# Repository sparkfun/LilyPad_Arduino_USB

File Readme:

LilyPad Arduino USB

This repository contains all of the design files for the LilyPad Arduino USB.

The "Firmware" directory contains a reference copy of the bootloader; the
"official" maintained version is in the Arduino source project. We'll try to
keep this updated if anything changes.

As with all SparkFun developments, we consider this to be "beerware"- should
you reuse it, please buy us a pint (of beer, orange juice, or braehg) at the
local next time you see one of us.

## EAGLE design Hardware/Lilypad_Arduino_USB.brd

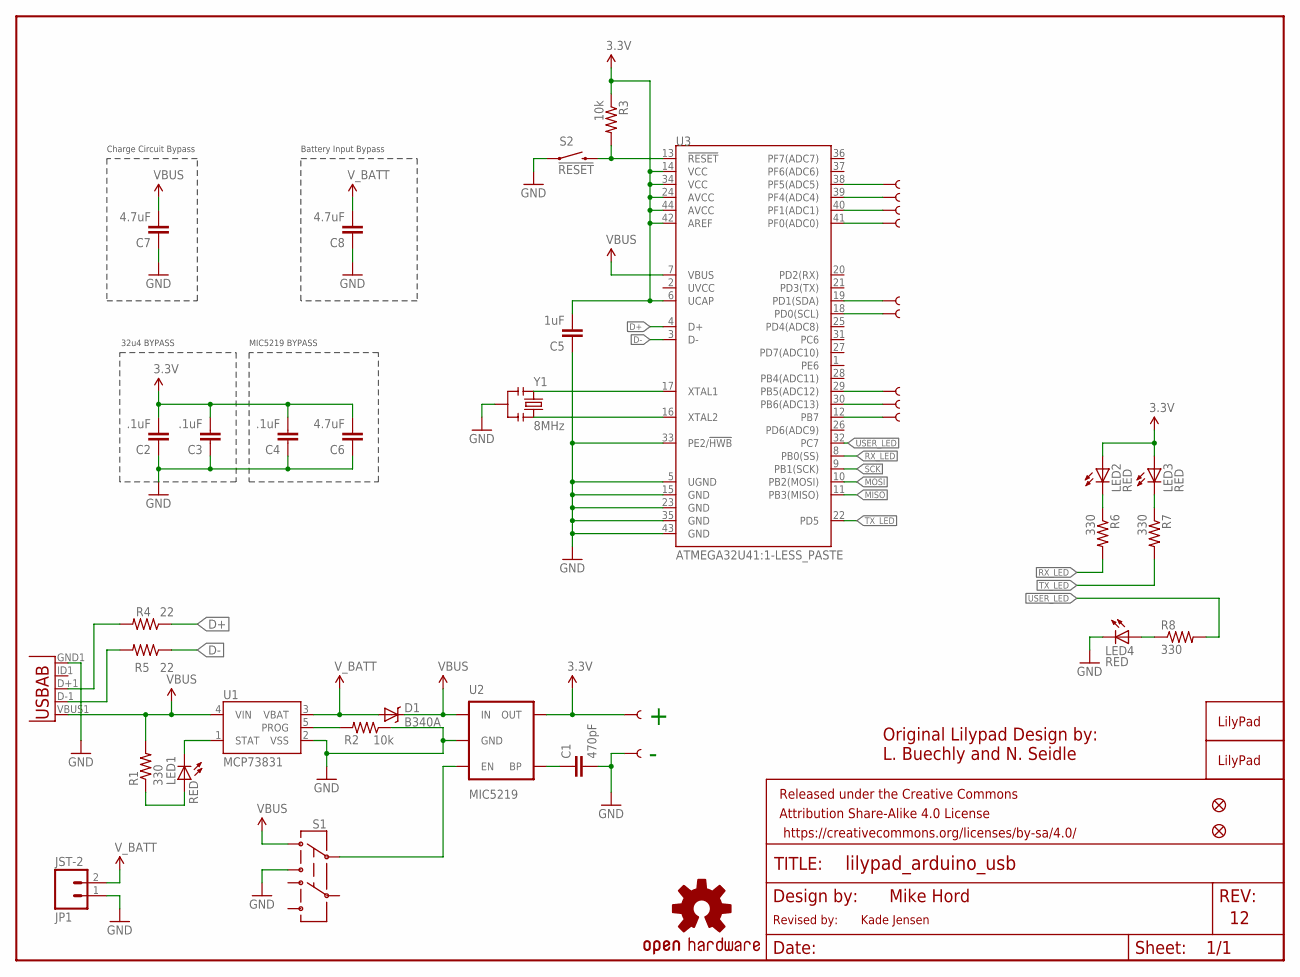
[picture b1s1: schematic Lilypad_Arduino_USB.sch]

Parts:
+: SEWTAP9; PETAL-LONG-1-2SIDE
-: SEWTAP9; PETAL-LONG-1-2SIDE
A2, A3, A4, A5: SEWTAP9; PETAL-LONG-1-2SIDE
C1: 470pF; 0603-CAP
C2, C3, C4: .1uF; 0603-CAP
C5: 1uF; 0603-CAP
C6: 4.7uF; 0603-CAP
C7, C8: 4.7uF; 1206
D1: B340A; SMA-DIODE
D5, D6, D9, D10, D11: SEWTAP9; PETAL-LONG-1-2SIDE
FRAME1: FRAME-LETTER; CREATIVE_COMMONS
JP1: JST-2; JST-2-SMD
JP2, JP3: FIDUCIAL1X2; FIDUCIAL-1X2
LED1, LED2, LED3, LED4: RED; LED-0603
R1, R6, R7, R8: 330; 0603-RES
R2, R3: 10k; 0603-RES
R4, R5: 22; 0603-RES
S1: SWITCH-DPDTAYZ0202; AYZ0202
S2: !RESET; TACTILE_SWITCH_SMD
U1: MCP73831; SOT23-5
U2: MIC5219; SOT23-5
U3: ATMEGA32U41:1-LESS_PASTE; QFN-44-NOPAD_1:1-LESS_PASTE
U5: USB-ABCONN-11794; USB-AB-MICRO-SMD_V03
U$1: LOGO-LPLPA; LOGO-LPA
U$5: OSHW-LOGOM; OSHW-LOGO-M
U$13: LOGO-LPLP; LOGO-LILYPAD
Y1: 8MHz; RESONATOR-SMD

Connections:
3.3V: +.1, C2.2, C3.2, C4.2, C5.2, C6.2, LED2.A, LED3.A, R3.1, U2.5 (OUT), U3.6 (UCAP), U3.14 (VCC), U3.24 (AVCC), U3.34 (VCC), U3.42 (AREF), U3.44 (AVCC)
5V: C7.2, D1.C, R1.2, S1.1, U1.4 (VIN), U2.1 (IN), U3.7 (VBUS), U5.VBUS1 (VBUS)
D+: R4.1, U3.4 (D+)
D-: R5.1, U3.3 (D-)
GND: -.1, C1.2, C2.1, C3.1, C4.1, C5.1, C6.1, C7.1, C8.1, JP1.1 (2), LED4.C, R2.1, S1.3, S2.1, U1.2 (VSS), U2.2 (GND), U3.5 (UGND), U3.15 (GND), U3.23 (GND), U3.33 (PE2/!HWB), U3.35 (GND), U3.43 (GND), U5.GND1 (GND), Y1.2
MISO: U3.11 (PB3(MISO))
MOSI: U3.10 (PB2(MOSI))
unnamed: LED2.C, R6.1
unnamed: S1.2, U2.3 (EN)
unnamed: LED1.A, R1.1
unnamed: LED1.C, U1.1 (STAT)
unnamed: U3.17 (XTAL1), Y1.1
unnamed: R2.2, U1.5 (PROG)
unnamed: U3.16 (XTAL2), Y1.3
unnamed: C1.1, U2.4 (BP)
unnamed: D11.1, U3.12 (PB7)
unnamed: D10.1, U3.30 (PB6(ADC13))
unnamed: D9.1, U3.29 (PB5(ADC12))
unnamed: D5.1, U3.19 (PD1(SDA))
unnamed: D6.1, U3.18 (PD0(SCL))
unnamed: A5.1, U3.41 (PF0(ADC0))
unnamed: A4.1, U3.40 (PF1(ADC1))
unnamed: A3.1, U3.39 (PF4(ADC4))
unnamed: A2.1, U3.38 (PF5(ADC5))
unnamed: LED4.A, R8.1
unnamed: R5.2, U5.D-1 (D-)
unnamed: R4.2, U5.D+1 (D+)
unnamed: LED3.C, R7.1
RESET: R3.2, S2.3 (2), U3.13 (!RESET)
RX_LED: R6.2, U3.8 (PB0(SS))
SCK: U3.9 (PB1(SCK))
TX_LED: R7.2, U3.22 (PD5)
USER_LED: R8.2, U3.32 (PC7)
V_BATT: C8.2, D1.A, JP1.2 (1), U1.3 (VBAT)

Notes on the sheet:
32u4 BYPASS
MIC5219 BYPASS
Mike Hord
Original Lilypad Design by:
L. Buechly and N. Seidle
Charge Circuit Bypass
Battery Input Bypass
Revised by:
Kade Jensen

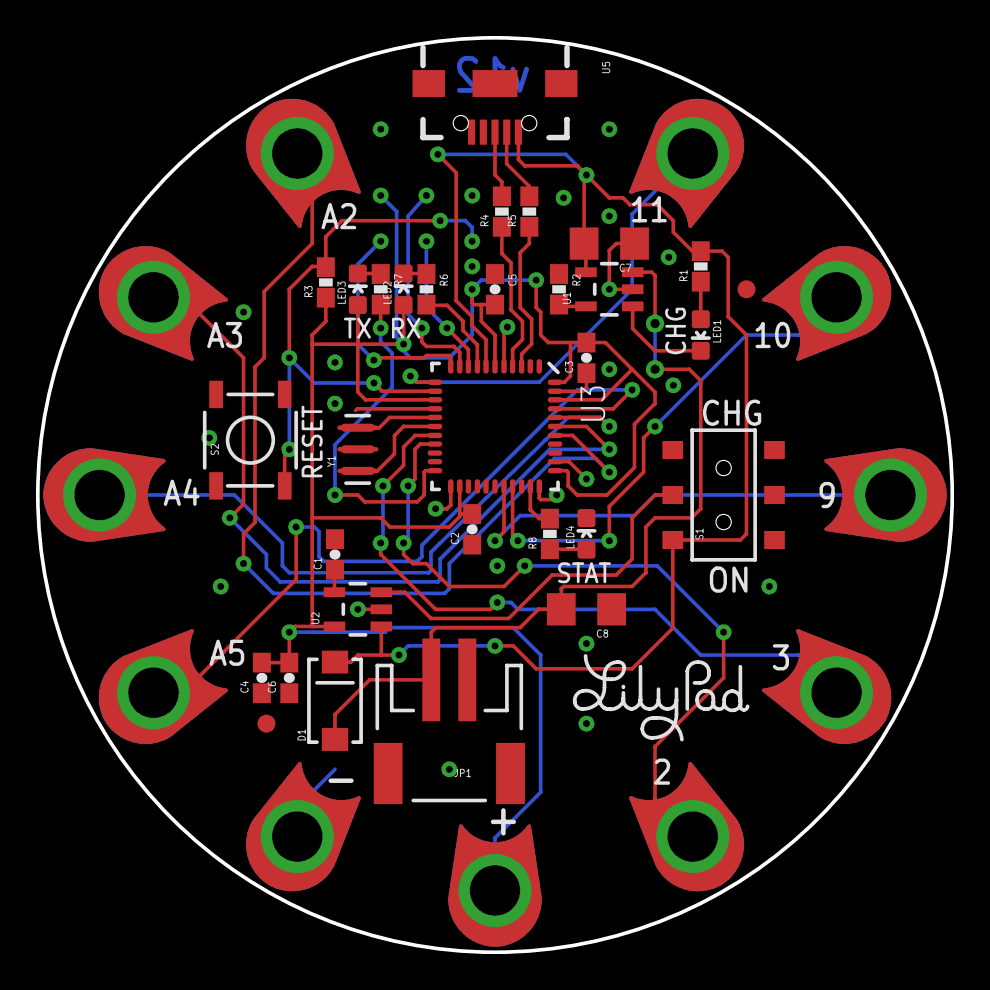
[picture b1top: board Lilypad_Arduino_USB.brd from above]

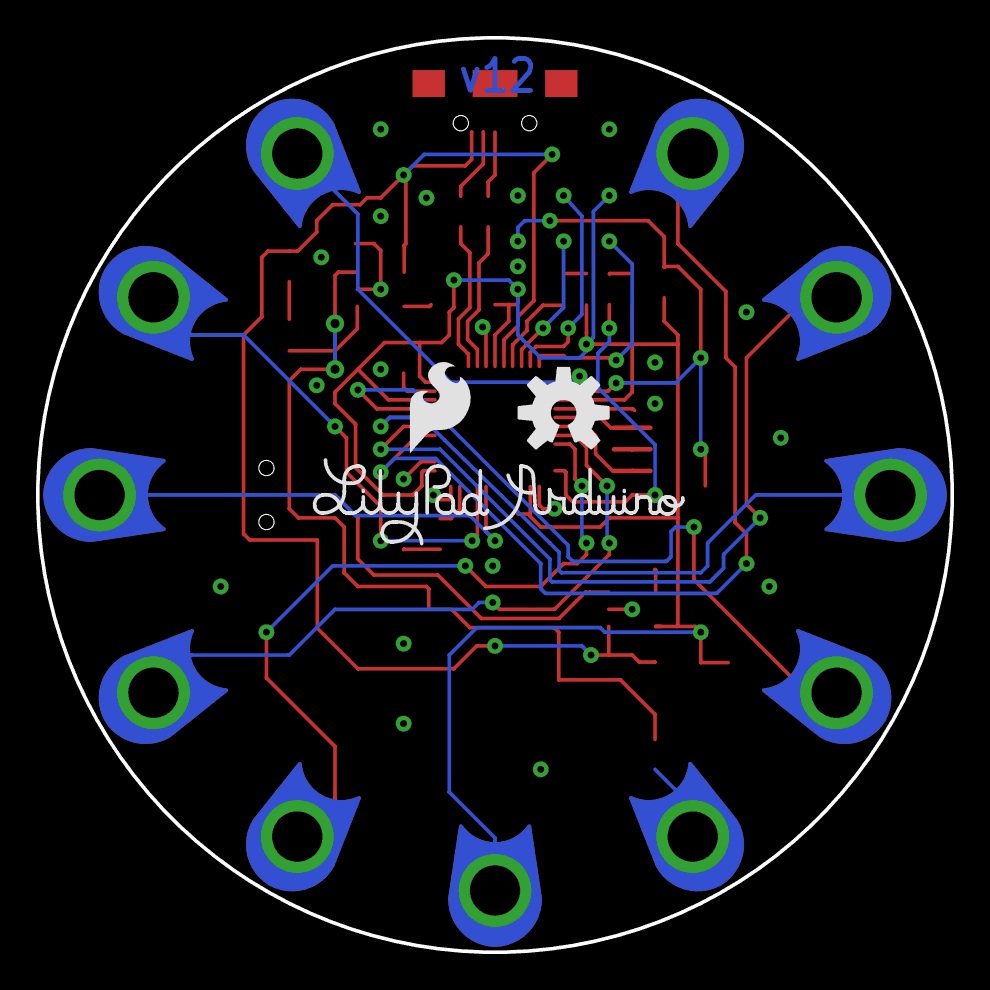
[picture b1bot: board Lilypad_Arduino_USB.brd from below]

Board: 2 copper layers, 50.8 x 50.8 mm, 47 parts (3 on the bottom side), 31 nets.

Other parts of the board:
U$7: SFE_LOGO_FLAME_.2

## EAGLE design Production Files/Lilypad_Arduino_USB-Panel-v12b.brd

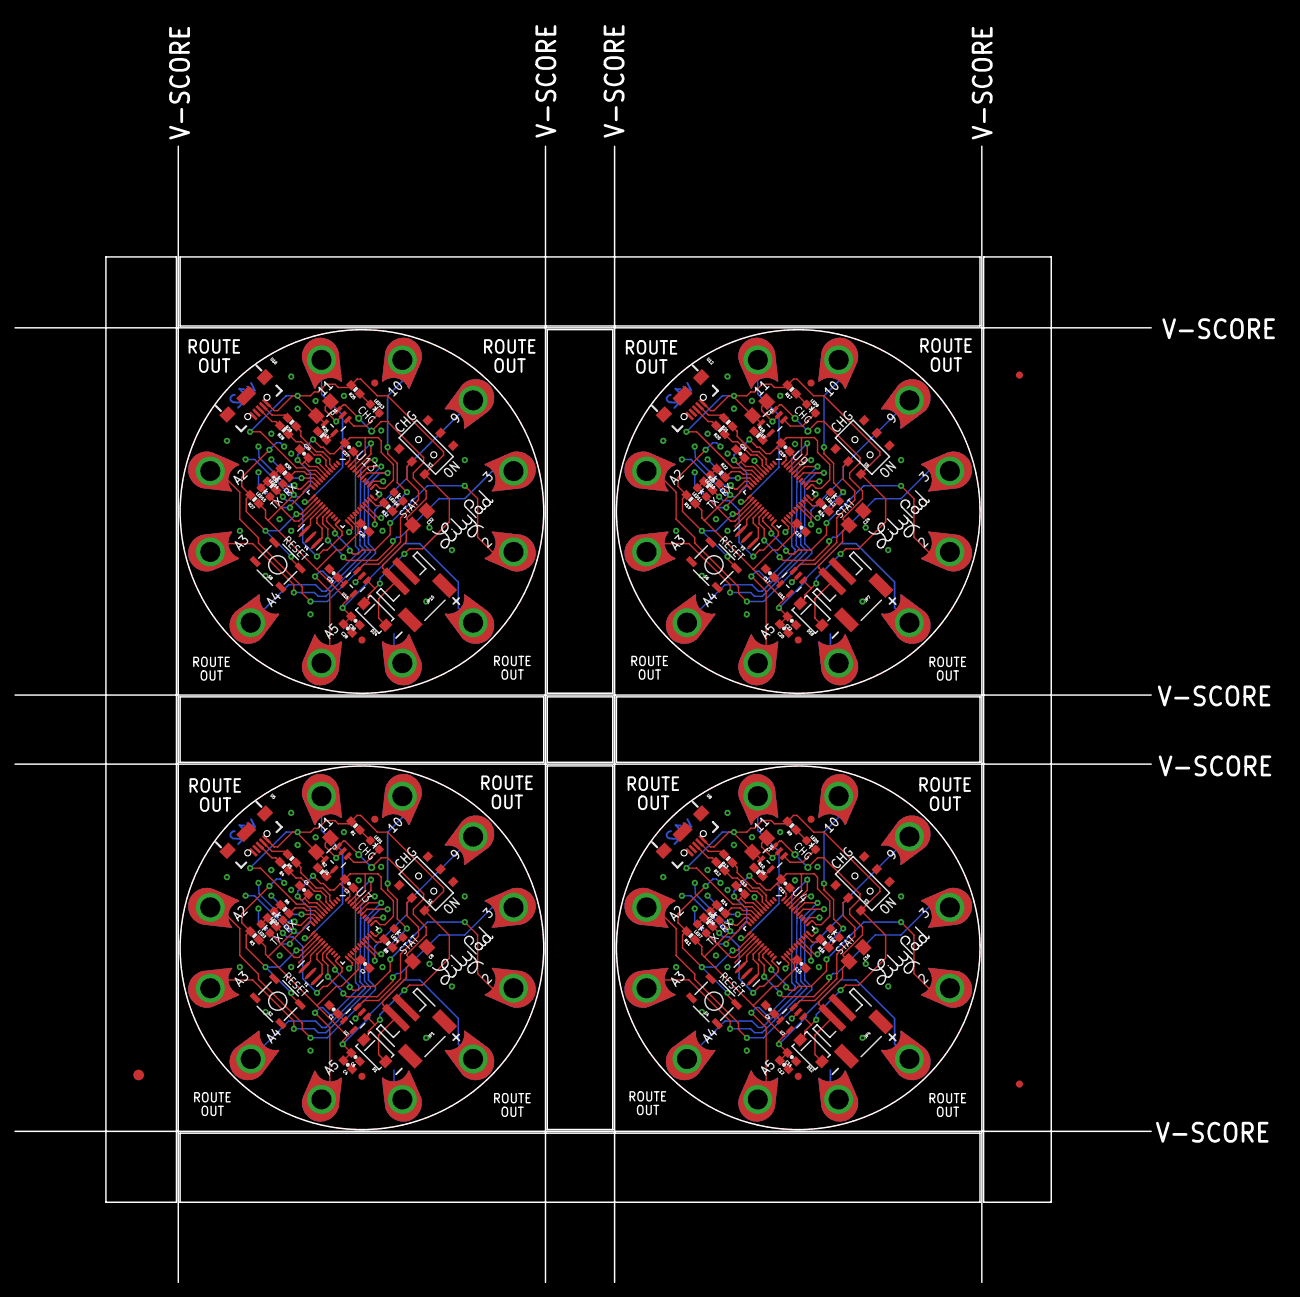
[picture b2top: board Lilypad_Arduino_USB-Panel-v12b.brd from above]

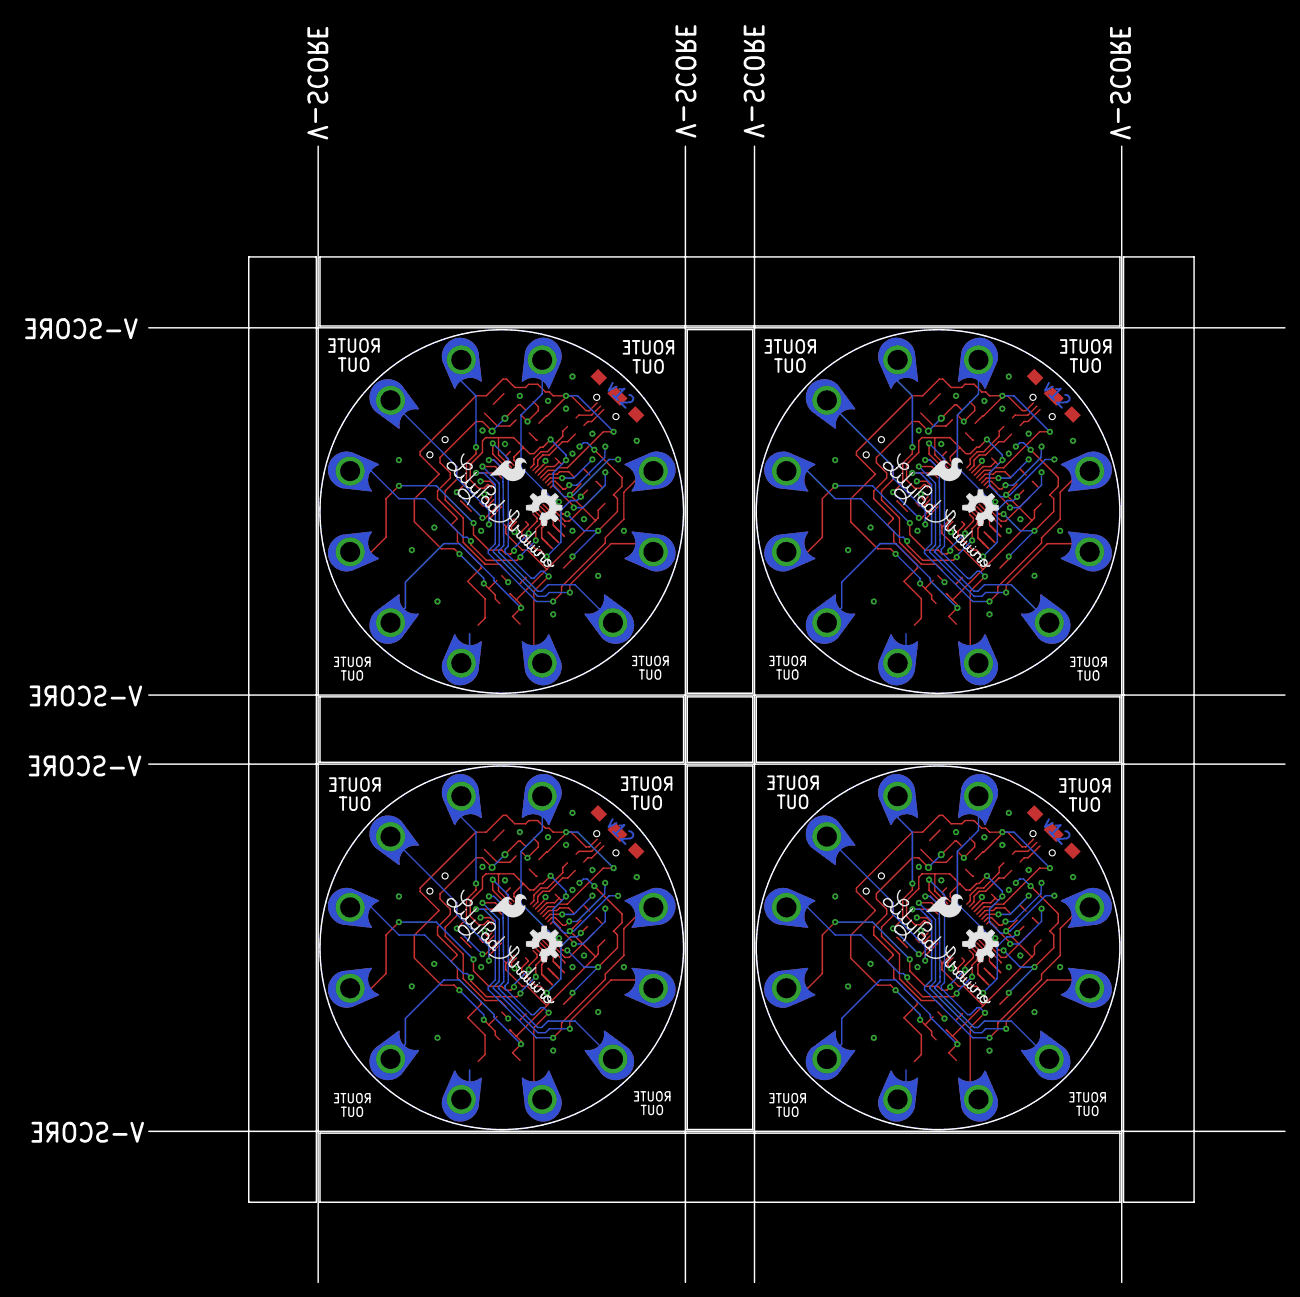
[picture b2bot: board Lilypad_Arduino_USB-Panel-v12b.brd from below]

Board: 2 copper layers, 158.8 x 158.8 mm, 187 parts (12 on the bottom side), 124 nets.

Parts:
+, +1, +2, +3: SEWTAP9; PETAL-LONG-1-2SIDE
-, -1, -2, -3: SEWTAP9; PETAL-LONG-1-2SIDE
A1, A2, A3, A4, A5, A6, A7, A8, A9, A10, A11, A12, A13, A14, A15, A16: SEWTAP9; PETAL-LONG-1-2SIDE
C1, C9, C17, C25: 470pF; 0603-CAP
C2, C3, C4, C10, C11, C12, C18, C19, C20, C26, C27, C28: .1uF; 0603-CAP
C5, C13, C21, C29: 1uF; 0603-CAP
C6, C14, C22, C30: 4.7uF; 0603-CAP
C7, C8, C15, C16, C23, C24, C31, C32: 4.7uF; 1206
D1, D12, D18, D24: B340A; SMA-DIODE
D2, D3, D4, D5, D6, D7, D8, D9, D10, D11, D13, D14, D15, D16, D17, D19, D20, D21, D22, D23: SEWTAP9; PETAL-LONG-1-2SIDE
E$1: FIDUCIAL-1.5X3
E$3, E$5: FIDUCIAL-1X2
JP1, JP4, JP7, JP10: JST-2; JST-2-SMD
JP2, JP3, JP5, JP6, JP8, JP9, JP11, JP12: FIDUCIAL1X2; FIDUCIAL-1X2
LED1, LED2, LED3, LED4, LED5, LED6, LED7, LED8, LED9, LED10, LED11, LED12, LED13, LED14, LED15, LED16: RED; LED-0603
R1, R6, R7, R8, R9, R14, R15, R16, R17, R22, R23, R24, R25, R30, R31, R32: 330; 0603-RES
R2, R3, R10, R11, R18, R19, R26, R27: 10k; 0603-RES
R4, R5, R12, R13, R20, R21, R28, R29: 22; 0603-RES
S1, S3, S5, S7: AYZ0202
S2, S4, S6, S8: !RESET; TACTILE_SWITCH_SMD
U1, U6, U10, U14: MCP73831; SOT23-5
U2, U7, U11, U15: MIC5219; SOT23-5
U3, U4, U9, U13: ATMEGA32U41:1-LESS_PASTE; QFN-44-NOPAD_1:1-LESS_PASTE
U5, U8, U12, U16: USB-AB-MICRO-SMD_V03
U$1, U$3, U$9, U$14: LOGO-LPLPA; LOGO-LPA
U$2, U$8, U$12, U$13: LOGO-LPLP; LOGO-LILYPAD
U$4, U$5, U$10, U$15: OSHW-LOGOM; OSHW-LOGO-M
U$6, U$7, U$11, U$16: SFE_LOGO_FLAME_.2
Y1, Y2, Y3, Y4: 8MHz; RESONATOR-SMD

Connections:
3.3V: +.1, C2.2, C3.2, C4.2, C5.2, C6.2, LED2.A, LED3.A, R3.1, U2.5, U3.6, U3.14, U3.24, U3.34, U3.42, U3.44
3.3V1: +1.1, C10.2, C11.2, C12.2, C13.2, C14.2, LED6.A, LED7.A, R11.1, U4.6, U4.14, U4.24, U4.34, U4.42, U4.44, U7.5
3.3V2: +2.1, C18.2, C19.2, C20.2, C21.2, C22.2, LED10.A, LED11.A, R19.1, U9.6, U9.14, U9.24, U9.34, U9.42, U9.44, U11.5
3.3V3: +3.1, C26.2, C27.2, C28.2, C29.2, C30.2, LED14.A, LED15.A, R27.1, U13.6, U13.14, U13.24, U13.34, U13.42, U13.44, U15.5
5V: C7.2, D1.C, R1.2, S1.1, U1.4, U2.1, U3.7, U5.VBUS1
5V1: C15.2, D12.C, R9.2, S3.1, U4.7, U6.4, U7.1, U8.VBUS1
5V2: C23.2, D18.C, R17.2, S5.1, U9.7, U10.4, U11.1, U12.VBUS1
5V3: C31.2, D24.C, R25.2, S7.1, U13.7, U14.4, U15.1, U16.VBUS1
D+: R4.1, U3.4
D+1: R12.1, U4.4
D+2: R20.1, U9.4
D+3: R28.1, U13.4
D-: R5.1, U3.3
D-1: R13.1, U4.3
D-2: R21.1, U9.3
D-3: R29.1, U13.3
GND: -.1, C1.2, C2.1, C3.1, C4.1, C5.1, C6.1, C7.1, C8.1, JP1.1, LED4.C, R2.1, S1.3, S2.1, U1.2, U2.2, U3.5, U3.15, U3.23, U3.33, U3.35, U3.43, U5.GND1, Y1.2
GND1: -1.1, C9.2, C10.1, C11.1, C12.1, C13.1, C14.1, C15.1, C16.1, JP4.1, LED8.C, R10.1, S3.3, S4.1, U4.5, U4.15, U4.23, U4.33, U4.35, U4.43, U6.2, U7.2, U8.GND1, Y2.2
GND2: -2.1, C17.2, C18.1, C19.1, C20.1, C21.1, C22.1, C23.1, C24.1, JP7.1, LED12.C, R18.1, S5.3, S6.1, U9.5, U9.15, U9.23, U9.33, U9.35, U9.43, U10.2, U11.2, U12.GND1, Y3.2
GND3: -3.1, C25.2, C26.1, C27.1, C28.1, C29.1, C30.1, C31.1, C32.1, JP10.1, LED16.C, R26.1, S7.3, S8.1, U13.5, U13.15, U13.23, U13.33, U13.35, U13.43, U14.2, U15.2, U16.GND1, Y4.2
unnamed: LED2.C, R6.1
unnamed: S1.2, U2.3
unnamed: LED1.A, R1.1
unnamed: LED1.C, U1.1
unnamed: U3.17, Y1.1
unnamed: R2.2, U1.5
unnamed: U3.16, Y1.3
unnamed: C1.1, U2.4
unnamed: D11.1, U3.12
unnamed: D10.1, U3.30
unnamed: D9.1, U3.29
unnamed: D5.1, U3.19
unnamed: D6.1, U3.18
unnamed: A5.1, U3.41
unnamed: A4.1, U3.40
unnamed: A3.1, U3.39
unnamed: A2.1, U3.38
unnamed: LED4.A, R8.1
unnamed: R5.2, U5.D-1
unnamed: R4.2, U5.D+1
unnamed: LED3.C, R7.1
unnamed: S3.2, U7.3
unnamed: LED5.A, R9.1
unnamed: LED5.C, U6.1
unnamed: R10.2, U6.5
unnamed: C9.1, U7.4
unnamed: D8.1, U4.12
unnamed: D7.1, U4.30
unnamed: D3.1, U4.29
unnamed: A7.1, U4.41
unnamed: A8.1, U4.40
unnamed: A6.1, U4.39
unnamed: A1.1, U4.38
unnamed: R13.2, U8.D-1
unnamed: R12.2, U8.D+1
unnamed: LED6.C, R14.1
unnamed: LED7.C, R15.1
unnamed: U4.17, Y2.1
unnamed: U4.16, Y2.3
unnamed: D2.1, U4.19
unnamed: D4.1, U4.18
unnamed: LED8.A, R16.1
unnamed: S5.2, U11.3
unnamed: LED9.A, R17.1
unnamed: LED9.C, U10.1
unnamed: R18.2, U10.5
unnamed: C17.1, U11.4
unnamed: D17.1, U9.12
unnamed: D16.1, U9.30
unnamed: D14.1, U9.29
unnamed: A11.1, U9.41
unnamed: A12.1, U9.40
unnamed: A10.1, U9.39
unnamed: A9.1, U9.38
unnamed: R21.2, U12.D-1
unnamed: R20.2, U12.D+1
unnamed: LED10.C, R22.1
unnamed: LED11.C, R23.1
unnamed: U9.17, Y3.1
unnamed: U9.16, Y3.3
unnamed: D13.1, U9.19
unnamed: D15.1, U9.18
unnamed: LED12.A, R24.1
unnamed: S7.2, U15.3
unnamed: LED13.A, R25.1
unnamed: LED13.C, U14.1
unnamed: R26.2, U14.5
unnamed: C25.1, U15.4
unnamed: D23.1, U13.12
unnamed: D22.1, U13.30
unnamed: D20.1, U13.29
unnamed: A15.1, U13.41
unnamed: A16.1, U13.40
unnamed: A14.1, U13.39
unnamed: A13.1, U13.38
unnamed: R29.2, U16.D-1
unnamed: R28.2, U16.D+1
unnamed: LED14.C, R30.1
unnamed: LED15.C, R31.1
unnamed: U13.17, Y4.1
unnamed: U13.16, Y4.3
unnamed: D19.1, U13.19
unnamed: D21.1, U13.18
unnamed: LED16.A, R32.1
RESET: R3.2, S2.3, U3.13
RESET1: R11.2, S4.3, U4.13
RESET2: R19.2, S6.3, U9.13
RESET3: R27.2, S8.3, U13.13
RX_LED: R6.2, U3.8
RX_LED1: R14.2, U4.8
RX_LED2: R22.2, U9.8
RX_LED3: R30.2, U13.8
TX_LED: R7.2, U3.22
TX_LED1: R15.2, U4.22
TX_LED2: R23.2, U9.22
TX_LED3: R31.2, U13.22
USER_LED: R8.2, U3.32
USER_LED1: R16.2, U4.32
USER_LED2: R24.2, U9.32
USER_LED3: R32.2, U13.32
V_BATT: C8.2, D1.A, JP1.2, U1.3
V_BATT1: C16.2, D12.A, JP4.2, U6.3
V_BATT2: C24.2, D18.A, JP7.2, U10.3
V_BATT3: C32.2, D24.A, JP10.2, U14.3

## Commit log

2012-12-10 Initial commit.
    This is the version of bootloader the shipped with
    the original LilyPad Arduino USB boards, and was released with
    Arduino IDE v1.0.2.
    This hardware is v10, and represents the initial shipping state of
    LilyPad Arduino USB boards.
2012-12-10 Change micro USB connector to more robust package.
2012-12-10 Panel for mass production
    Reoriented the board 45 degrees so that the USB connector doesn't hang
    over where production techs need to run the depanelizing blade along
    v-scores.
2012-12-11 Moved the panelized file into a production directory to keep the customer-oriented files more tidy and less confusing.
2012-12-13 Changed version number in both files.
    Masked via at .35, .275 to provide a test point for the charge circuit.
    Add USR mask on the user control LED to make it more clear what it does.
    Closes issues 1 and 2.
2013-09-09 Quality Control Revision to PCB layout
    Changed:
    - Updated all 0402 footprints to 0603
    - Updated with new 1:1 footprint of 32u4 IC
    - Rerouted all traces straight away from IC
    - Added trestrict under IC to mitigate gnd plane
    - Moved crystal closer to IC
2013-10-04 Created Panel
2013-10-04 Revert "Created Panel"
    This reverts commit 475b5a8a9a08da90b89791f5318257dca302304d.
2013-10-04 Created Panel v12
    correct this time...
2013-10-07 Minor silk changes
    Moved A4 silk so it doesn't get cut off by the button pads. Added
    Sparkfun flames in bottom silk.
2013-10-07 Added silk to reset button
    Added silk to reset button
2013-10-07 Re-created Panel
    Re-created panel v12
2013-11-15 Fixing D+ trace connection
    ID line on USB connector was routed to D+ on micro and D+ on USB
    connector was unrouted. Fixed now.
2013-12-05 Minor Silk fixes
    Silk for "A4" and "STAT" was getting cut off. Moved slightly to fix.
2014-03-27 More updated packages
    1.) New 0603 LED packages
    2.) New resonator package
    3.) Moved reset button over to allow silk to be correct size.
    4.) Added attribution to board file
    5.) Minor trace reroutes for new packages
    6.) New 32u4 package variant that changes paste layer.
2014-04-07 Fixing wonky trace under C1
    Correcting a trace overshoot on C1 near vreg.
2014-04-21 Updated silk and two traces
    1.) Changed bottom silk to not interfere with vias
    2.) Changed two traces to be more efficient
2014-04-22 created panel v12
2021-12-13 New production panel v12b - strength tabs and v-scores
2025-06-27 Update Readme.md
    Updating links.

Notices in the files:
parts and their libraries:
SparkFun-PowerIC: Licensing: CC v3.0 Share-Alike You are welcome to use this library for commercial purposes.
SparkFun-Aesthetics: Released under the Creative Commons Attribution Share-Alike 4.0 License
SparkFun-Aesthetics: https://creativecommons.org/licenses/by-sa/4.0
